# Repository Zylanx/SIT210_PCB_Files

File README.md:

# SIT210_PCB_Files

These are EAGLE files.
I keep thinking "Maybe EAGLE will be better this time" and every time it disappoints and is somehow worse.

# NOTE
I realise the board I am connecting to doesn't actually need the voltage divider. But when I realised that, I left it in because it is just too simple and boring otherwise.
I am going to upload a version without it which should work fine too.

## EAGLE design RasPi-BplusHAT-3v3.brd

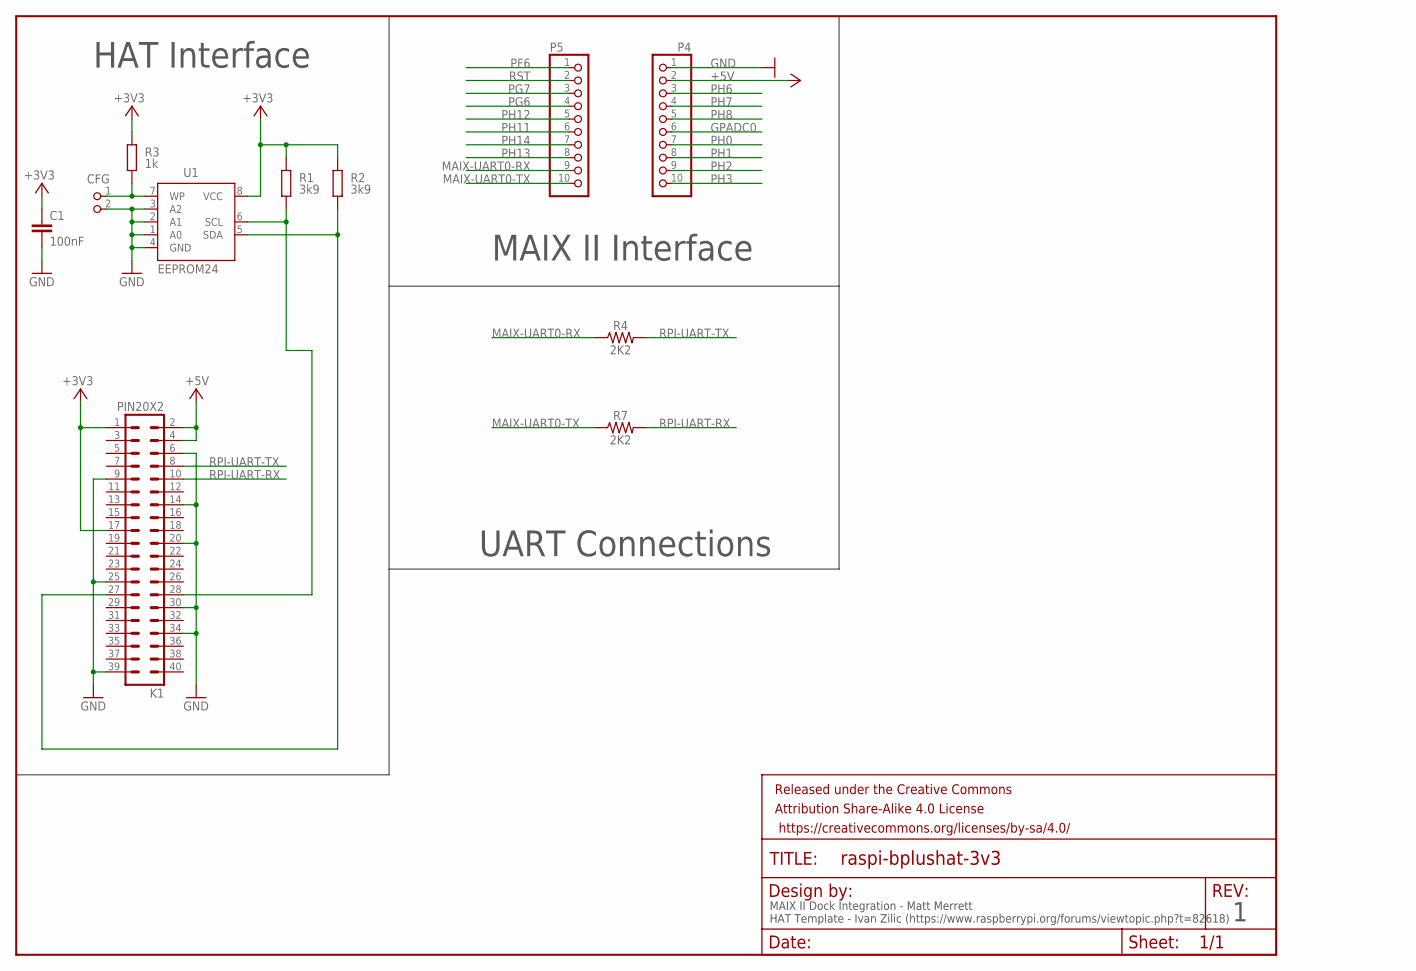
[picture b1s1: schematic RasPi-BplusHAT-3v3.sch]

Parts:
C1: 100nF; C0805K
CFG: PIN2_100; PIN_W_2
FRAME1: FRAME-LETTER; CREATIVE_COMMONS
K1: PIN20X2; PIN_20X2
P4, P5: PINHD-1X10; 1X10
R1, R2: 3k9; M0805; TOLERANCE 5%
R3: 1k; M0805; TOLERANCE 5%
R4, R7: 2K2; AXIAL-0.3
U1: EEPROM24; SOIC8

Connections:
+3V3: C1.1, K1.1, K1.17, R1.2, R2.2, R3.2, U1.8 (VCC)
+5V: K1.2, K1.4, P4.2
GND: C1.2, CFG.2, K1.6, K1.9, K1.14, K1.20, K1.25, K1.30, K1.34, K1.39, P4.1, U1.1 (A0), U1.2 (A1), U1.3 (A2), U1.4 (GND)
GPADC0: P4.6
MAIX-UART0-RX: P5.9, R4.P$1 (1)
MAIX-UART0-TX: P5.10, R7.P$1 (1)
unnamed: K1.28, R1.1, U1.6 (SCL)
unnamed: K1.27, R2.1, U1.5 (SDA)
unnamed: CFG.1, R3.1, U1.7 (WP)
PF6: P5.1
PG6: P5.4
PG7: P5.3
PH0: P4.7
PH1: P4.8
PH2: P4.9
PH3: P4.10
PH6: P4.3
PH7: P4.4
PH8: P4.5
PH11: P5.6
PH12: P5.5
PH13: P5.8
PH14: P5.7
RPI-UART-RX: K1.10, R7.P$2 (2)
RPI-UART-TX: K1.8, R4.P$2 (2)
RST: P5.2

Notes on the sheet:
HAT Interface
MAIX II Interface
UART Connections
MAIX II Dock Integration - Matt Merrett HAT Template - Ivan Zilic (https://www.raspberrypi.org/forums/viewtopic.php?t=82618)

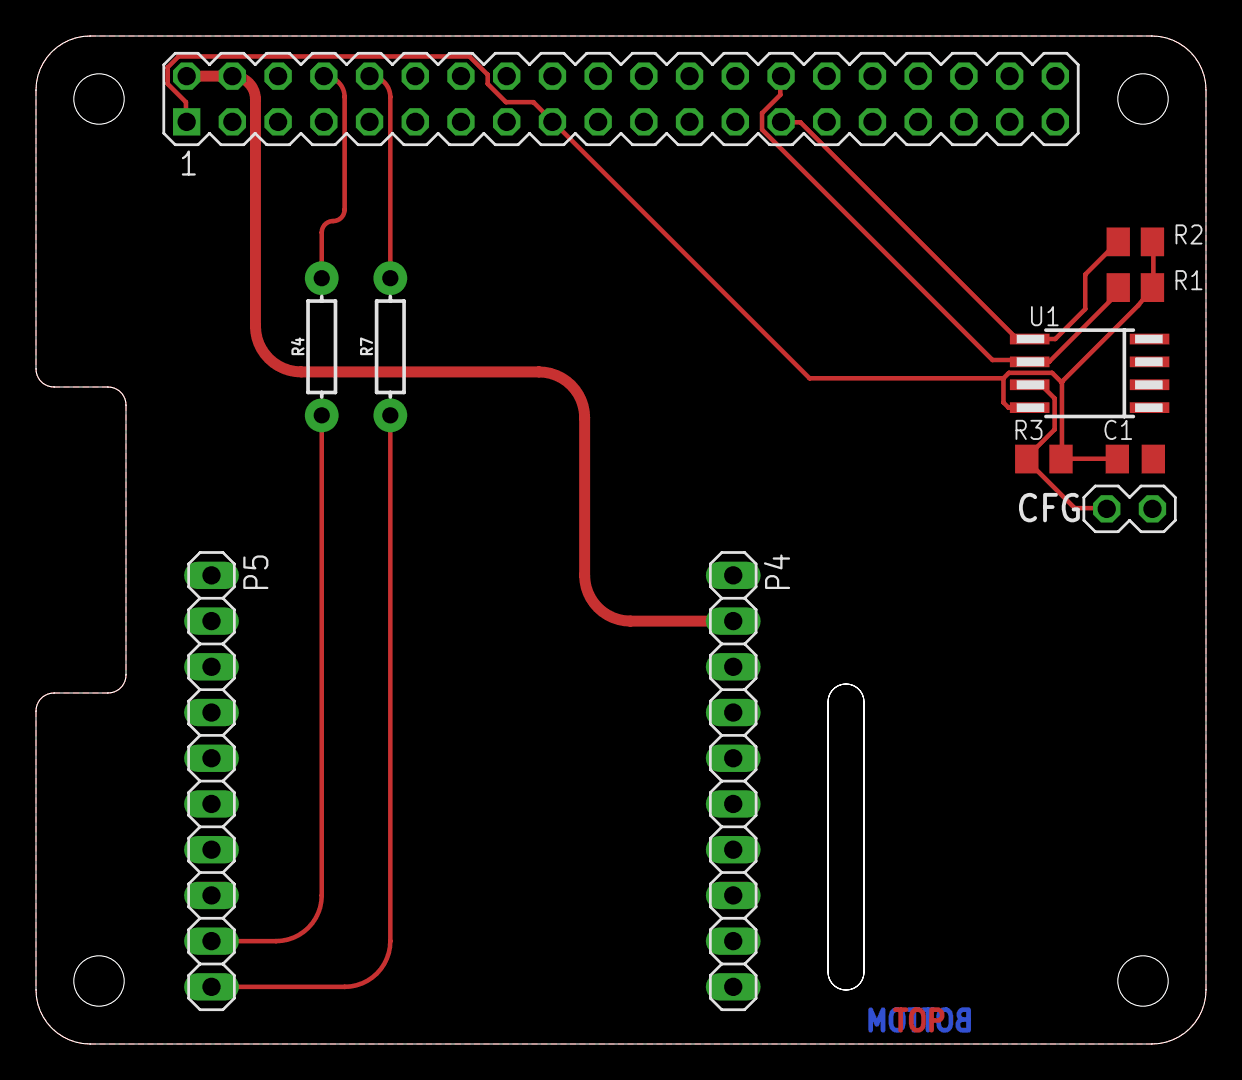
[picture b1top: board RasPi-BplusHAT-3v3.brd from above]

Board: 2 copper layers, 65.0 x 56.0 mm, 12 parts (0 on the bottom side), 10 nets.

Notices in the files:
parts and their libraries:
SparkFun-Aesthetics: Licensing: Creative Commons ShareAlike 4.0 International - https://creativecommons.org/licenses/by-sa/4.0
SparkFun-Aesthetics: Released under the Creative Commons Attribution Share-Alike 4.0 License
SparkFun-Aesthetics: https://creativecommons.org/licenses/by-sa/4.0
